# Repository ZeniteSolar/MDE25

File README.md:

<!-- PROJECT LOGO -->
<br />
<div align="center">

  <h3 align="center">Módulo de Direção Elétrica 2025 (MDE25)</h3>
</div>

# Visão Geral do Sistema

O sistema de direção elétrica do barco solar é composto por duas placas interligadas, uma de controle e outra de potência. O propósito do sistema é ser capaz de controlar o leme do barco conforme comandos recebidos pela rede CAN do barco enviados pelo Módulo Interface de Controle (MIC).

O barco contém atualmente a revisão [MDE22](https://github.com/ZeniteSolar/MDE22). Como pode ser visto, atualmente o barco contém uma bateria auxiliar de 12V dedicada para alimentar o sistema de direção elétrica, algo que não é tão proveitoso, sendo que o barco possui um banco de baterias principal que é mais que capacitado para alimentar o sistema de direção elétrica. Assim sendo, a bateria auxiliar implica em peso e eletrônica adicional, sendo que requer um Módulo de Carregamento de Bateria Auxiliar.

Tendo em vista a fundamentação acima, a revisão 2025 (MDE25) tem por objetivo:

* Remover a bateria auxiliar de 12V
* Utilizar o banco de baterias principal para alimentar o sistema de direção elétrica
* Melhorar aspectos gerais do sistema, velocidade de resposta, confiabilidade, etc.

Assim sendo, os requisitos abaixo foram definidos, vale notar que vários dos valores já são conhecidos de revisões anteriores, por isso não serão abordados aqui, mas podem ser encontrados no GitHub da [Zenite Solar](https://github.com/ZeniteSolar).

## Requisitos

* Tensão de entrada: 10-60V
* Tensão de saída: 10-60V
* Corrente média nominal: 20-30A
* Corrente média máxima: 42A
* Corrente de pico máxima: 80A
* Full Bridge (Reversão Completa)

## Estrutura do Projeto

Para o desenvolvimento do sistema, tendo em vista que a fabricação das placas foi realizada localmente, ou seja, não se atinge qualidade de empresas especializadas, foi decidido que o sistema seria desenvolvido em duas placas, uma de controle e outra de potência. Permitindo tolerância a erros de fabricação maiores e facilitando a fabricação e manutenção em geral.

---

### 1. Placa de Controle

A placa de controle é responsável por realizar a parte lógica do sistema, bem como gerar as tensões baixas, $V_{DDs}$ em geral e $V_{drive}$. Assim sendo, é constituída majoritariamente por um microcontrolador, um transceptor CAN, e um conjunto de conversores Step-Down / LDOs responsáveis por gerar as tensões necessárias para o sistema.

#### Componentes Principais

* **Microcontrolador:** STM32L431
* **Comunicação:** Rede CAN a 500 kbit/s baseado no transceptor MCP2561.
* **Interfaces:**
  * Conector CAN (também fornece 18 V para alimentação)
  * UART / ST-LINK para programação e depuração
  * Conector para sensor de posição do leme (potenciômetro)
  * Conectores para encoder e fim de curso (redundância)

---

### 2. Placa de Potência

A placa de potência é um sistema extremamente simples, sendo suas únicas funções controlar o motor utilizando uma Ponte H conforme sinais de PWM recebidos da placa de controle, prover sinais de medição, ou seja (Tensão de entrada, Tensão de saída e Corrente de entrada), sendo esses já tratados para serem convertidos pelo ADC do microcontrolador da placa de controle.

## Componentes Principais

* **Topologia:** Ponte H (full-bridge) com dois drivers UCC27211DDAR e quatro MOSFETs BSC093N15NS5.
* **Sensoriamento:**
  * Corrente: shunt de 1 mΩ + amplificador de instrumentação (INA283)
* Tensão: divisor resistivo com filtro passa-baixa de 40 Hz, objetivo de reduzir ruído de chaveamento/ringing.
* **Conectores:**
  * Alimentação principal via KRE (baterias chumbo-ácido 30-42 V ou lítio até 60 V)
  * Saída para motor modelo CIM (modelo FR801‑001)
* **Dissipação térmica:**
  * 5 vias de cobre (Ø 0,7 mm) por MOSFET
  * Thermal pad de 1 mm de espessura e 1 cm² por MOSFET
  * Dissipador montado entre as placas

---

# Fluxo de Sinal e Potência

1. **Entrada de Comando:**
   A placa MIC mede a posição do volante e transmite via CAN o setpoint da posição do leme através da mensagem `CAN_MSG_MIC19_MDE_ID`.

2. **Leitura e Controle:**
   O STM32L431 recebe o comando via CAN, valida o ID e seta o setpoint no controlador PID (utilizando apenas ganho proporcional devido a testes anteriores revelarem conflito entre piloto e ganho integral), que por consequência ajusta o PWM dos drivers conforme o erro entre o setpoint e a posição do leme.

3. **Ponte H:**
   Os drivers UCC27211 acionam os MOSFETs BSC093N15NS5 conforme o PWM gerado. Sendo que pode ser controlada tanto a direção quanto a velocidade do motor através da direção da corrente estabelecida pelo chaveamento e o duty cycle do PWM.

4. **Motor e Feedback:**
   O motor movimenta o leme, cuja posição é retroalimentada via um potenciômetro de 10 kΩ acoplado ao eixo e lido pelo ADC do STM32L431, que por sua vez atualiza a posição atual no controlador PID.

5. **Proteções e Limites:**
   * Monitoramento de corrente via shunt
   * Faixa de tensão de entrada: 10 V a 60 V
   * Faixa de tensão de saída: 0 V a 12 V (Motor projetado para 12 V)
   * Corrente média operacional: 20–30 A (No uso normal do barco)
   * Corrente contínua máxima: 42 A (com eixo travado até a queima) com picos de 80 A.
   * Potência média máxima: 425 W (Teste realizado até a queima da ponte H por incapacidade de dissipação e consequente dessolda dos MOSFETs)
   * Dissipador alcançou 60 C após 2 minutos de teste com reversão contínua, ou seja, ir de um extremo ao outro do leme (condição não usual)

---

# Etapas da Placa de Potência

## Entrada

Função de receber a tensão da bateria principal e alimentar a ponte H. Possui um fusível de 20 A para proteção e um banco de capacitores para estabilização da tensão que será utilizada pela ponte H.

* Conector KRE de alimentação (bateria principal)
* Fusível de 20 A
* Shunt de 1 mΩ para medição de corrente
* Filtros:
  * 2 × 470 µF eletrolíticos
  * 4 × 1 µF cerâmicos para redução de ripple e compensação de indutâncias parasitas

---

## Drivers

Os drivers são responsáveis por converter o sinal de PWM (Baixa tensão 3.3V e baixa capacidade de corrente) para um sinal de gate apropriado para os MOSFETs, além de que, por se tratar de uma ponte H completa, é necessário um driver com capacidade de chavear MOSFETs high-side e low-side. Assim sendo, foram utilizados dois drivers UCC27211DDAR, um para cada braço da ponte H. Mais especificações podem ser encontradas no datasheet do driver [UCC27211DDAR](https://www.ti.com/lit/ds/symlink/ucc27211.pdf) e no texto abaixo.

* 2 × UCC27211DDAR (meia ponte, tecnologia bootstrap)
* Acionamento complementar com limitação de corrente de gate por resistores de 62 Ω, ajustado em laboratório conforme notas de aplicação [External Gate Resistor Design Guide for Gate Drivers](https://www.ti.com/lit/ab/slla385a/slla385a.pdf)
* Resistores de 10 kΩ entre gate e source para evitar operação na região linear quando em alta impedância.
* Proteções adicionais conforme [Bootstrap Circuitry Selection for Half-Bridge
Configurations](https://www.ti.com/lit/an/slua887a/slua887a.pdf):
  * 2 diodos para proteção
  * Resistor de 2 Ω para limitar corrente de bootstrap

---

## Ponte H (MOSFETs + Snubber)

A ponte H é composta por quatro MOSFETs, dois para cada braço da ponte H, sendo que cada braço é composto por um MOSFET high-side e um MOSFET low-side, permitindo a reversão completa do motor e controle de velocidade através do duty cycle do PWM.

* 4 × BSC093N15NS5 (150 V, 87 A, R<sub>DS(on)</sub> = 9,3 mΩ)
* Proteção por snubber com TVS de 111 V (breakdown), 160 V (clamping)
* Estratégia de chaveamento:

  * Um braço da ponte permanece fixo (conduzindo), o outro chaveia.
  * O braço fixo alterna de acordo com o sentido do motor.
  * Para evitar sobrecarga no bootstrap, é garantido no controlador que o MOSFET acionado no braço fixo seja sempre o MOSFET low-side, assim sendo, o bootstrap não será completamente descarregado, pois o MOSFET high-side não conduzirá, evitando entrada na região linear dos MOSFETs.

---

## Sensor de Corrente (Entrada)

* Shunt de 1 mΩ + amplificador INA283 (ganho de 50 V/V)
* Saturação a 3,3 V → Corrente máxima medida ≈ 66 A

---

## Sensor de Tensão (Entrada e Saída)

* Divisor resistivo para adequar até 60 V para 2,6 V
* Filtro passa-baixa de 100 nF a 40 Hz
* Margem contra saturação do ADC e interferência do zener de proteção (3,3 V)
> Para medição da tensão de saída deve ser utilizado modo diferencial do ADC, assim sendo possível a medição da tensão tanto positiva quanto negativa. Isso ocorre pois, dependendo do sentido da corrente, a tensão de saída pode ser positiva ou negativa.

---

# Placa de Controle

A placa de controle, como já mencionado, é responsável por realizar as seguintes funções:

* Gerar níveis de tensão baixos (15V, 5V, 3.3V), note-se que o conector RJ45 da rede CAN já fornece 18V.
* Receber o setpoint desejado pelo piloto através da rede CAN.
* Monitorar a posição do leme através do potenciômetro.
* Gerar uma ação de controle para o motor através do PWM.

* Alimentação lógica e dos drivers por 18 V da rede CAN
* Comunicação CAN conforme padrão do barco solar
* MCU STM32L431:
  * Leitura de posição do leme (potenciômetro via ADC)
  * Implementação do controle proporcional
  * Geração do PWM de controle para os drivers

# Implementação do Projeto

Dado que praticamente todos os componentes já eram impostos (Já existiam no inventário da Zenite Solar e não podiam ser adquiridos novos atualmente), o projeto foi simplesmente a realização dos requisitos. Assim sendo, foi utilizado o software KiCad para a elaboração do projeto.

[Esquemático da Placa de Controle](./hardware/control/outputs/control.pdf)

[Esquemático da Placa de Potência](./hardware/power/outputs/power.pdf)

Com o projeto em mãos, foi realizada a fabricação das placas, ambas placas foram fabricadas localmente utilizando-se a técnica de fotolitografia com tinta UV e uma impressora de resina Elegoo Mars 2 PRO para a exposição UV. Os químicos utilizados foram os padrões para esse tipo de processo (Carbonato de Sódio 1%, Percloreto de Ferro e Acetona). Após a manufatura, ambas placas foram estanhadas, tendo em vista que o ambiente de trabalho é propenso à corrosão e o estanhamento melhora a vida útil das placas.

## Placa de Controle

## Placa de Potência

## Placa de controle montada

## Placa de potência montada

## Sistema de dissipação térmica

## MDE25 - Montagem Final

---

# Testes

Para monitoramento/ajustes, um pequeno aplicativo Python foi desenvolvido, pode-se encontrar [Aqui](./firmware/Extra/TelemetryPanel/panel.py). Esse aplicativo foi utilizado para verificar comportamento do sistema e ajustar o controlador PID.

## Simples exemplo de um teste em hardware real (Direção + Leme) aproximando uma resposta ao degrau

## Simples exemplo de um teste em hardware real (Direção + Leme) aproximando um setpoint seguindo uma onda triangular

Como pode ser visto, o sistema operou corretamente conforme o esperado, abaixo mais detalhes sobre os testes são apresentados.

## Limite a limite velocidade constante

Foi realizado um teste com o volante indo de limite a limite a velocidade constante:

* O motor leva cerca de 1s para atingir o extremo oposto (Ótimo tempo de resposta)
* Na reversão, consome cerca de 40 A por 500 ms
* Corrente estabiliza em torno de 11 A após aceleração
* Temperatura do dissipador atingiu 60 C após 2 min de teste contínuo (Esse comportamento de teste contínuo não é um caso esperado que o piloto realize em operação normal)

## Teste de queima

Após a validação do sistema, desejou-se testar a capacidade de sobrecarga do MDE25, para assim entender os limites e como o sistema vem a falhar. Para isso, o eixo do leme foi travado e o piloto comandou a direção de um extremo ao outro do leme.

As métricas do painel de monitoramento foram as seguintes:

Foi necessário cerca de 30 segundos para que o sistema entrasse em sobrecarga e viesse a queima. Como pode ser visto pelo painel, no momento em que entra em sobrecarga, a tensão na bateria principal caiu cerca de 4V. Indo de aproximadamente 38V para 34V, isso demonstra que um estresse muito grande foi aplicado ao sistema, tendo em vista que se trata de um banco de baterias de chumbo com alta capacidade de corrente. Após a queima, o sistema foi desmontado e averigou-se a causa da queima.

## Detalhes da queima e notas sobre o sistema

Dado que os MOSFETs utilizados realizam a sua troca de calor com o dissipador por um pad térmico, ou seja, a transferência não é realizada pelo case do componente, mas sim pelo seu pad de dreno, é necessário que a placa seja capaz de conduzir esse calor de forma efetiva para o dissipador, assim foram feitas vias de cobre (5 vias de 0.7mm para cada MOSFET). Segue abaixo a foto das vias térmicas.

Como pode ser observado, um dos conjuntos de vias ficou apenas com 3 vias efetivamente transferindo calor, pois 2 acabaram sendo lixadas pelo processo de fabricação, isso resultou com que o MOSFET associado com essas vias viesse a sobreaquecer e dessoldar, não sendo o calor diretamente a causa da queima, mas sim a dessolda do MOSFET que resultou em uma gota de solda dando curto no braço da ponte H e após isso gerando a queima. Segue foto do MOSFET queimado.

<div style="text-align: center; max-width: 20%; margin: 0 auto;">
  
</div>

# Notas extras sobre estimativa da Indutância do Motor

Para estimar a indutância do motor, utilizamos o ripple de corrente observado em regime permanente com o motor em velocidade constante.

## Parâmetros do teste:

* Corrente média: **11 A**
* Ripple de corrente: **10%** → $\Delta I = 1{,}1\,\text{A}_{pp}$
* Tensão de alimentação: **36 V**
* Duty cycle: **40%**
* Frequência de PWM: **20 kHz** (→ período $T_s = 50\,\mu\text{s}$)
* Topologia: **Ponte H full-bridge com modulação bipolar**

## Modelo de cálculo:

Assumindo modulação bipolar, a variação de corrente durante o ciclo de comutação é dada por:

$$
\Delta I = \frac{2 \cdot V \cdot D \cdot T_s}{L}
\Rightarrow
L = \frac{2 \cdot V \cdot D \cdot T_s}{\Delta I}
$$

Substituindo os valores:

$$
L = \frac{2 \cdot 36\,\text{V} \cdot 0{,}4 \cdot 50 \times 10^{-6}\,\text{s}}{1{,}1\,\text{A}}
= \frac{1{,}44 \cdot 10^{-3}}{1{,}1}
\approx 1{,}31\,\text{mH}
$$

## Resultado:

A indutância estimada do motor é:

$$
\boxed{L \approx 1{,}31\;\text{mH}}
$$

# Sobre o Firmware

## Arquitetura de Software

O firmware está organizado em módulos funcionais especializados:
- **Core/control**: Implementação do controlador PID
- **Core/pwm**: Geração de sinais PWM para ponte H
- **Core/sense**: Aquisição de dados via ADC
- **Core/CAN**: Servidor de comunicação CAN
- **Core/uart_server**: Interface de debug e configuração
- **Core/telemetry**: Sistema de monitoramento
- **Core/status**: Gerenciamento de estado e feedback sonoro

## Configuração do Sistema

O firmware possui diversos parâmetros que podem ser ajustados para otimizar o sistema para as necessidades do usuário, esses podem ser ajustados no arquivo de configuração [config.h](./firmware/Core/Inc/config.h).

## Módulos de Firmware

### 1. Módulo de Controle (Core/control)

#### Funcionalidades Principais
O módulo implementa um controlador PID digital completo (control.c) com as seguintes características técnicas:

**Parâmetros de Controle:**
- Ganho Proporcional (Kp): 2.8 (inicial, configurável)
- Ganho Integral (Ki): 0.0 (inicial, configurável)
- Ganho Derivativo (Kd): 0.0 (inicial, configurável)
- Janela de média móvel: 15 amostras para filtragem de setpoint para evitar mudança abrupta de setpoint.

**Algoritmo PID:**
```
error = setpoint - feedback
integral += error * dt
integral = clamp(integral, -0.1, 0.1)  // Anti-windup
derivative = (error - error_previous) / dt
output = Kp * error + Ki * integral + Kd * derivative
```

**Características de Implementação:**
- **Filtragem de Setpoint** (control.c): Média móvel de 15 amostras para suavizar comandos de entrada e reduzir oscilações
- **Saturação de Saída**: Limitação entre -1.0 e +1.0 com zona morta configurável
- **Anti-windup**: Limitação da integral entre -0.1 e 0.1 para evitar saturação
- **Período Dinâmico**: Baseado na frequência real de amostragem do ADC
- **Lock de Setpoint**: Capacidade de travamento para operação manual

### 2. Módulo PWM (Core/pwm)

#### Geração de Sinais PWM
O módulo controla a ponte H através de dois canais PWM complementares (pwm.c):

**Especificações Técnicas:**
- **Timer**: TIM1 (Advanced Timer) utilizado para gerar os sinais PWM.
- **Frequência Base**: 24 kHz (configurável acima de 1.3 kHz)
- **Resolução**: 16 bits
- **Canais**: CH1 e CH2 com saídas complementares (CHxN)

**Compensação de Tensão** (pwm.c):
O sistema implementa compensação automática baseada na tensão de entrada:
```
max_duty = PWM_MAX_OUT_VOLTAGE / clamped_input_voltage;
effective_duty = map(input_duty, -1.0, 1.0, -max_duty, max_duty);
```

**Características de Segurança:**
- **Zona Morta**: Configurável (-0.06 a +0.06) para evitar vibrações e perda de energia sem realização de movimento útil.

#### Configurações
- **Tensão Máxima de Saída (Ajustável)**: 12V
- **Faixa de Tensão de Entrada**: 24V a 60V
- **Dead Time**: Configurado para proteção da ponte H, otimizado em laboratório para melhor tempo sem gerar curto no braço.

### 3. Módulo de Sensoriamento (Core/sense)

#### Aquisição de Dados ADC
Sistema de conversão analógico-digital de 4 canais simultâneos (sense.c:10-16):

**Canais de Conversão:**
```
typedef enum {
  ADC_RANK_CURRENT_CONTROL_POINT = 0U,  // Posição do leme
  ADC_RANK_INPUT_VOLTAGE = 1U,           // Tensão de entrada
  ADC_RANK_OUTPUT_VOLTAGE = 2U,          // Tensão de saída
  ADC_RANK_INPUT_CURRENT = 3U,           // Corrente de entrada
} adc_ranks_t;
```

**Características Técnicas:**
- **Resolução**: 16 bits (65535 níveis) (Com Oversample, dado cru 12 bits)
- **Modo**: Conversão contínua via DMA
- **Trigger**: Timer 2 (frequência configurável) atrelado também a atualização da malha de controle.
- **Buffer**: Circular DMA para aquisição contínua

**Calibração e Linearização:**
Cada canal possui calibração específica (sense.c), calibrações do ADC podem ser feitas utilizando o seguinte [script](./firmware/Extra/ADC_Linearization/linearization.py):
- **Tensão de Entrada**: `V = 0.001150 * ADC - 0.088064`
- **Tensão de Saída**: `V = 0.002327 * ADC - 73.731254`
- **Posição**: `P = (ADC * 2.0 / 65535.0) - 1.0` (normalizada ±1.0)
- **Corrente**: `I = ADC * 3.3 / 65535.0` (referência 3.3V)

### 4. Servidor CAN (Core/CAN)

#### Protocolo de Comunicação
Implementa cliente CAN para recepção de comandos do MIC19 (can_server.c):

**Filtro CAN** (can_server.c):
- **Modo**: ID Mask para filtragem seletiva
- **Banco**: 0 (FIFO0)
- **Máscara**: 0x7FF (11 bits de ID padrão)

**Especificações do Protocolo:**
- **ID da Mensagem**: 31 (CAN_MSG_MIC19_MDE_ID)
- **Comprimento**: 4 bytes
- **Frequência**: 50 Hz
- **Assinatura**: 240 (CAN_SIGNATURE_MIC19)

**Estrutura da Mensagem:**
```
Byte 0: Assinatura (240)
Byte 1: Position_L (8 bits baixos)
Byte 2: Position_H (8 bits altos)
Byte 3: Reservado
```

**Processamento de Dados** (can_server.c):

Normalização do setpoint -1.0 a 1.0:

```
uint16_t position = rxData[1] | (rxData[2] << 8);
float steering_angle = (position / 1024.0f) * 2.0f - 1.0f;
```

#### Sistema de Watchdog
**Timeout de Comunicação** (can_server.c):
- **Timer**: TIM7 para detecção de perda de comunicação
- **Reset Automático**: Contador zerado a cada mensagem válida
- **Ação de Timeout**: Setpoint zerado e status de desconexão. Gera sinal sonoro de sequência específica de BEEP no motor. Reconexão também irá resultar em sinal sonoro de sequência específica de BEEP no motor.

### 5. Servidor UART (Core/uart_server)

#### Interface de Debug e Configuração
Sistema de comunicação serial para debug e ajuste de parâmetros (uart_server.c):

**Protocolo de Comando:**
- **Formato**: `<comando:valor>`
- **Delimitadores**: `<` (início) e `>` (fim)
- **Parser**: Máquina de estados para robustez
- **Buffer**: 128 bytes com buffer circular

**Comandos Disponíveis:**
```
'D': Set PWM duty cycle (-1.0 a 1.0)
'F': Set PWM frequency (Hz)
'p': Set PID proportional gain
'i': Set PID integral gain
'd': Set PID derivative gain
's': Set ADC sampling frequency
'L': Lock/unlock PWM (1/0)
'R': System reset
```

#### Implementação do Parser
**Máquina de Estados** (uart_server.c):
```
UART_SERVER_STATE_WAIT_START      -> Aguarda '<'
UART_SERVER_STATE_WAIT_TERMINATOR -> Coleta dados até '>'
UART_SERVER_STATE_NEW_MESSAGE     -> Mensagem completa
UART_SERVER_STATE_ERROR           -> Overflow ou erro
```
### 6. Sistema de Telemetria (Core/telemetry)

#### Estrutura de Dados
Coleta e transmite métricas do sistema (telemetry.h):

```
typedef struct {
  uint16_t preamble;           // 0x5A54
  float sense_input_voltage;   // Tensão de entrada
  float sense_input_current;   // Corrente de entrada
  float sense_output_voltage;  // Tensão de saída
  float sense_control_point;   // Posição atual
  float control_setpoint;      // Setpoint desejado
  float control_error;         // Erro de controle
  float pwm_duty;             // Duty cycle nominal
  float pwm_effective_duty;   // Duty cycle efetivo
  uint8_t status_connected;   // Status de conexão
} telemetry_t;
```

**Características de Transmissão:**
- **Frequência**: 40 Hz (intervalo de 25ms)
- **Interface**: UART a 115200 bps
- **Formato**: Printf formatado para debug
- **Habilitação**: Condicional via DEBUG_TELEMETRY_ENABLE

#### Saída de Debug
Formato de telemetria (telemetry.c):
```
"VI:%f, II:%f, VO:%f, CP:%f, SP:%f, ER:%f, D:%f, ED:%f, ST:%hu\n"
```

### 7. Módulo de Status (Core/status)

#### Sistema de Feedback Sonoro
Gerencia indicação sonora de estado do sistema (status.c):

**Sequências de Status:**
- **Conexão**: 3 tons crescentes (Baixo → Médio → Alto)
- **Desconexão**: 3 tons decrescentes (Alto → Médio → Baixo)
- **Desconectado**: Tom único alto

**Parâmetros Sonoros:**
```
#define STATUS_TONE_FREQUENCY_LOW_HZ    2093.0f  // C7
#define STATUS_TONE_FREQUENCY_MEDIUM_HZ 2794.0f  // F7
#define STATUS_TONE_FREQUENCY_HIGH_HZ   4186.0f  // C8
#define STATUS_TONE_DURATION_S          0.16f
#define STATUS_TONE_PWM_VOLUME          0.70f
```

#### Implementação Técnica
**Geração de Tom** (status.c):
- **Timer**: TIM6 para base de tempo
- **Modulação**: PWM alternado entre +70% e -70%
- **Cálculo de Frequência**: `repetitions = duration / (1/frequency)`
- **Callback**: Sistema de callbacks encadeados para sequências

**Controle de Estado:**
- **Variável Global**: `device_connected` para rastreamento
- **Transições**: Apenas em mudanças de estado
- **Proteção**: Evita múltiplas execuções da mesma sequência

### 8. Utilitários Matemáticos (utils.h)

```
float clampf(float value, float min, float max);
// Limita valor entre mínimo e máximo

float passf(float value, float replace, float cut_min, float cut_max);
// Zona morta - substitui valores dentro de faixa

float mapf(float value, float min_in, float max_in, float min_out, float max_out);
// Mapeia valor de uma faixa para outra
```

### Configuração de Periféricos
**Timers Utilizados:**
- **TIM1**: PWM principal (24 kHz, centro-alinhado)
- **TIM2**: Trigger para ADC (frequência configurável)
- **TIM6**: Base de tempo para status sonoro
- **TIM7**: Watchdog de comunicação CAN

**DMA Channels:**
- **ADC1**: Conversão contínua 4 canais
- **UART1**: Recepção com idle detection

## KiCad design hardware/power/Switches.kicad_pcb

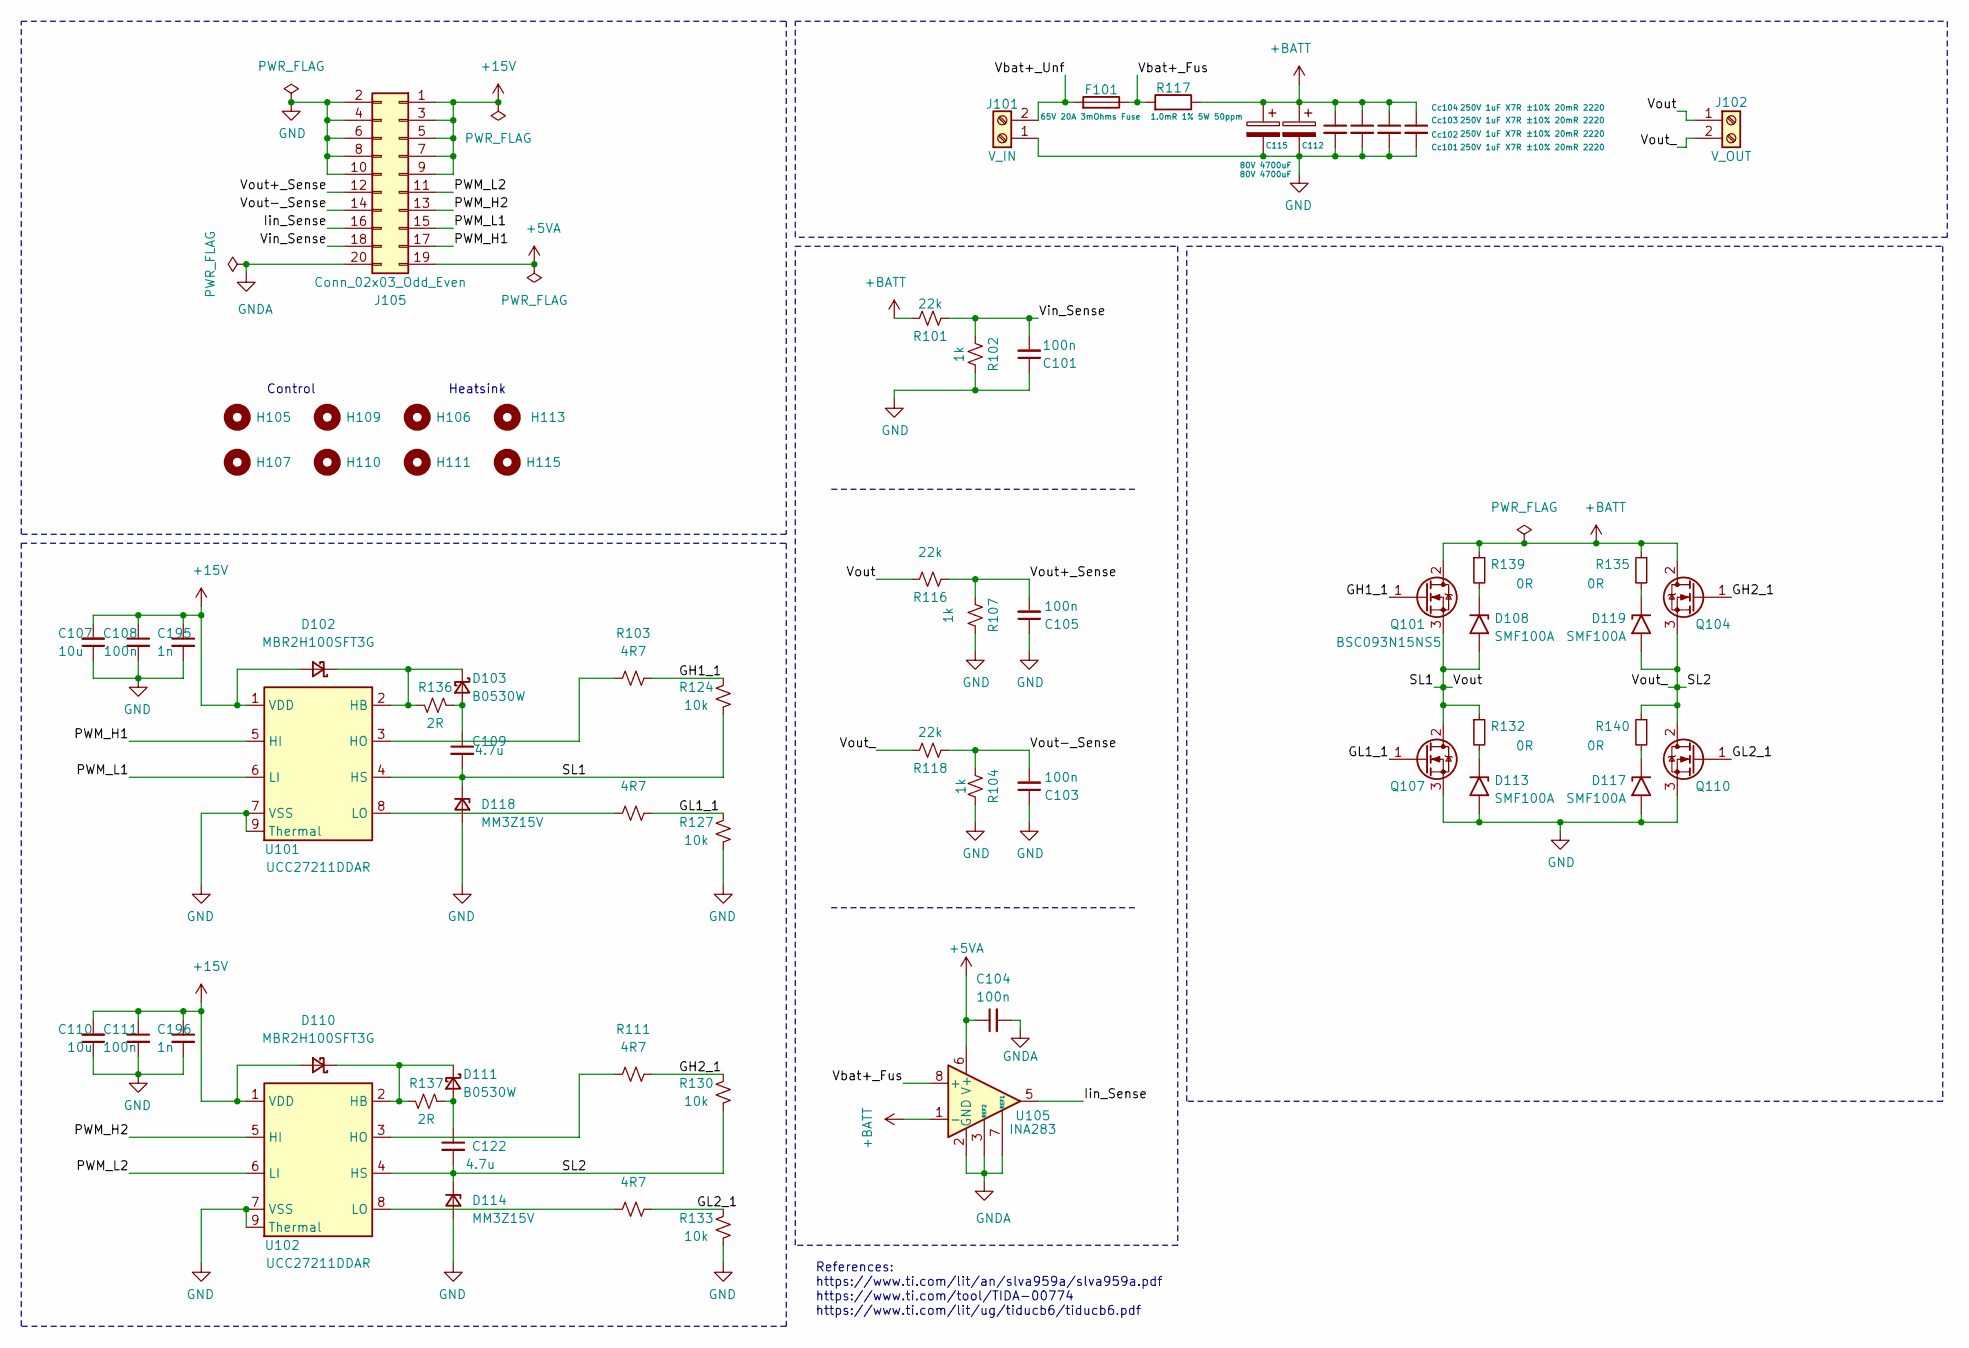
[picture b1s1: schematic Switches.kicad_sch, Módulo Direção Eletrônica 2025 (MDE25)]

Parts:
C101, C103, C104, C105, C108, C111: 100n; C_0805_2012Metric_Pad1.18x1.45mm_HandSolder
C107, C110: 10u; C_1210_3225Metric_Pad1.33x2.70mm_HandSolder
C109, C122: 4.7u; C_1210_3225Metric_Pad1.33x2.70mm_HandSolder
C112, C115: 80V 4700uF; CP_Radial_D12.5mm_P5.00mm
C195, C196: 1n; C_0805_2012Metric_Pad1.18x1.45mm_HandSolder
Cc101, Cc102, Cc103, Cc104: 250V 1uF X7R ±10% 20mR 2220; C_2220_5650Metric
D102, D110: MBR2H100SFT3G; D_SOD-123F
D103, D111: B0530W; D_SOD-123F
D108, D113, D117, D119: SMF100A; D_SOD-123F
D114, D118: MM3Z15V; D_SOD-123F
F101: 65V 20A 3mOhms Fuse; S6125-F
H105, H106, H107, H109, H110, H111, H113, H115: MountingHole; MountingHole_3.5mm_Pad
J101: V_IN; TerminalBlock_MaiXu_MX126-5.0-02P_1x02_P5.00mm
J102: V_OUT; TerminalBlock_MaiXu_MX126-5.0-02P_1x02_P5.00mm
J105: Conn_02x03_Odd_Even; PinHeader_2x10_P2.54mm_Vertical
Q101, Q104, Q107, Q110: BSC093N15NS5; TDSON-8-3
R101, R116, R118: 22k; R_0805_2012Metric_Pad1.20x1.40mm_HandSolder
R102, R104, R107: 1k; R_0805_2012Metric_Pad1.20x1.40mm_HandSolder
R103, R106, R111, R114: 4R7; R_0805_2012Metric_Pad1.20x1.40mm_HandSolder
R117: 1.0mR 1% 5W 50ppm; R_2512_6332Metric_Pad1.40x3.35mm_HandSolder
R124, R127, R130, R133: 10k; R_0805_2012Metric_Pad1.20x1.40mm_HandSolder
R132, R135, R139, R140: 0R; R_0805_2012Metric_Pad1.20x1.40mm_HandSolder
R136, R137: 2R; R_0805_2012Metric_Pad1.20x1.40mm_HandSolder
U101, U102: UCC27211DDAR; SOIC-8-1EP_3.9x4.9mm_P1.27mm_EP2.514x3.2mm
U105: INA283; SOIC-8_3.9x4.9mm_P1.27mm

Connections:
+5VA: C104.1, J105.19, U105.6 (V+)
+15V: C107.2, C108.1, C110.2, C111.1, C195.1, C196.1, D102.2 (A), D110.2 (A), J105.1, J105.3, J105.5, J105.7, J105.9, U101.1 (VDD), U102.1 (VDD)
+BATT: C112.1, C115.1, Cc101.1, Cc102.1, Cc103.1, Cc104.1, Q101.2 (D), Q104.2 (D), R101.2, R117.1, R135.1, R139.1, U105.1 (-)
/GH1_1: Q101.1 (G), R103.1, R124.2
/GH2_1: Q104.1 (G), R111.1, R130.2
/GL1_1: Q107.1 (G), R106.1, R127.2
/GL2_1: Q110.1 (G), R114.1, R133.2
/Iin_Sense: J105.16, U105.5
/PWM_H1: J105.17, U101.5 (HI)
/PWM_H2: J105.13, U102.5 (HI)
/PWM_L1: J105.15, U101.6 (LI)
/PWM_L2: J105.11, U102.6 (LI)
/SL1: C109.2, D108.2 (A2), D118.1 (K), J102.1, Q101.3 (S), Q107.2 (D), R116.2, R124.1, R132.1, U101.4 (HS)
/SL2: C122.2, D114.1 (K), D119.2 (A2), J102.2, Q104.3 (S), Q110.2 (D), R118.2, R130.1, R140.1, U102.4 (HS)
/Vbat+_Fus: F101.1, R117.2, U105.8 (+)
/Vbat+_Unf: F101.2, J101.2
/Vin_Sense: C101.2, J105.18, R101.1, R102.1
/Vout+_Sense: C105.2, J105.12, R107.1, R116.1
/Vout-_Sense: C103.2, J105.14, R104.1, R118.1
GND: C101.1, C103.1, C105.1, C107.1, C108.2, C110.1, C111.2, C112.2, C115.2, C195.2, C196.2, Cc101.2, Cc102.2, Cc103.2, Cc104.2, D113.2 (A2), D114.2 (A), D117.2 (A2), D118.2 (A), J101.1, J105.2, J105.4, J105.6, J105.8, J105.10, Q107.3 (S), Q110.3 (S), R102.2, R104.2, R107.2, R127.1, R133.1, U101.7 (VSS), U101.9 (Thermal), U102.7 (VSS), U102.9 (Thermal)
GNDA: C104.2, J105.20, U105.2 (GND), U105.3 (REF2), U105.7 (REF1)
unnamed: D102.1 (K), D103.1 (K), R136.1, U101.2 (HB)
unnamed: C109.1, D103.2 (A), R136.2
unnamed: D108.1 (A1), R139.2
unnamed: D110.1 (K), D111.1 (K), R137.1, U102.2 (HB)
unnamed: C122.1, D111.2 (A), R137.2
unnamed: D113.1 (A1), R132.2
unnamed: D117.1 (A1), R140.2
unnamed: D119.1 (A1), R135.2
unnamed: R103.2, U101.3 (HO)
unnamed: R106.2, U101.8 (LO)
unnamed: R111.2, U102.3 (HO)
unnamed: R114.2, U102.8 (LO)

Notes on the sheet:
Control
References: https://www.ti.com/lit/an/slva959a/slva959a.pdf https://www.ti.com/tool/TIDA-00774 https://www.ti.com/lit/ug/tiducb6/tiducb6.pdf
Heatsink

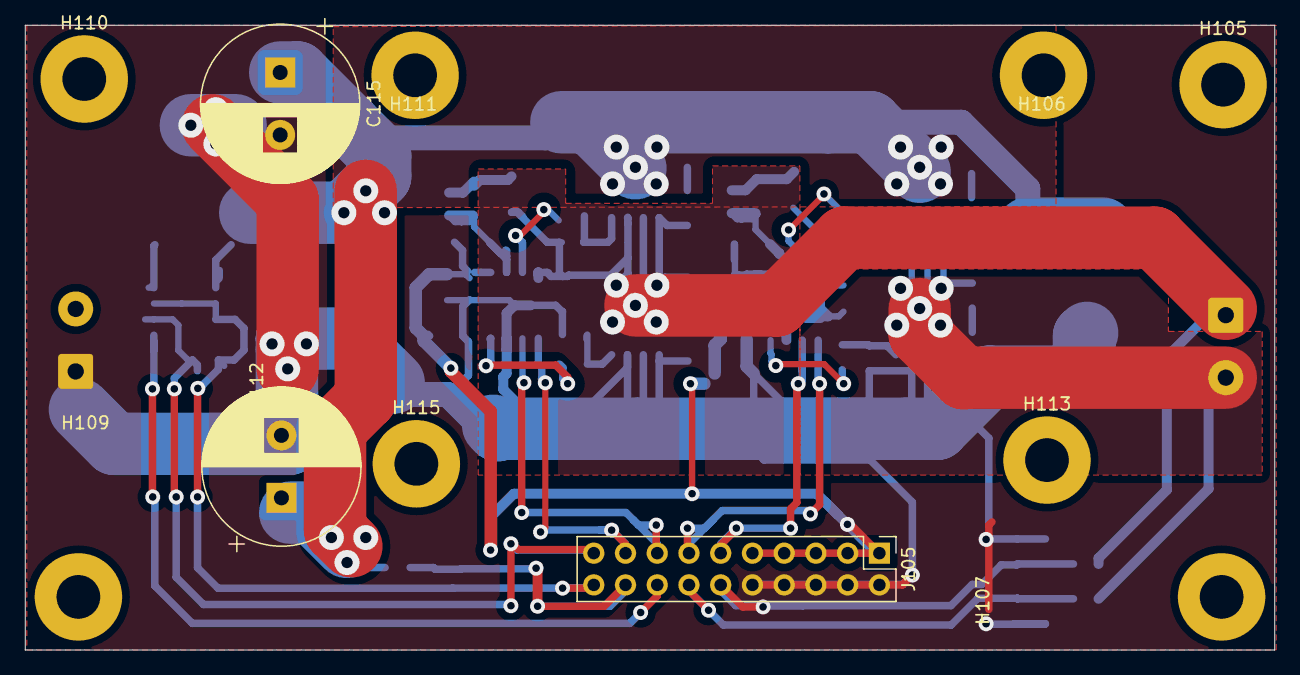
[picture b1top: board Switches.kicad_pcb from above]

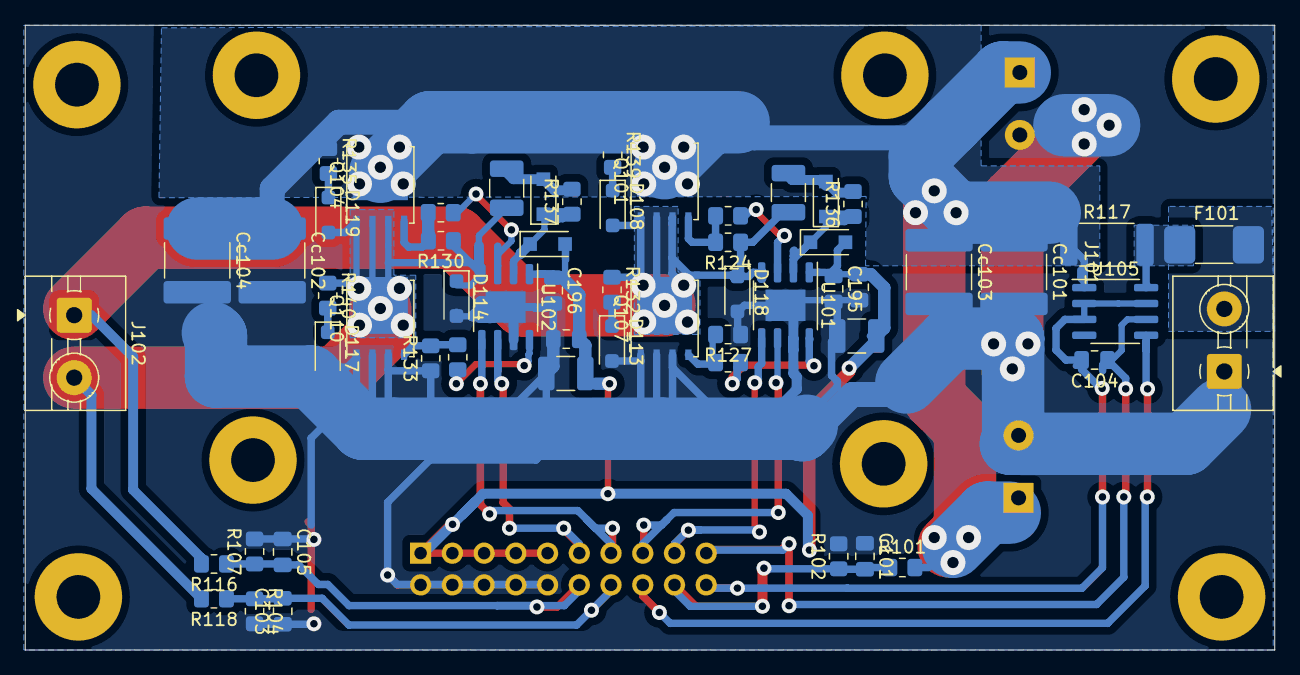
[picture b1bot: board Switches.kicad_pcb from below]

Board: 2 copper layers, 100.0 x 50.0 mm, 68 parts (57 on the bottom side), 33 nets.

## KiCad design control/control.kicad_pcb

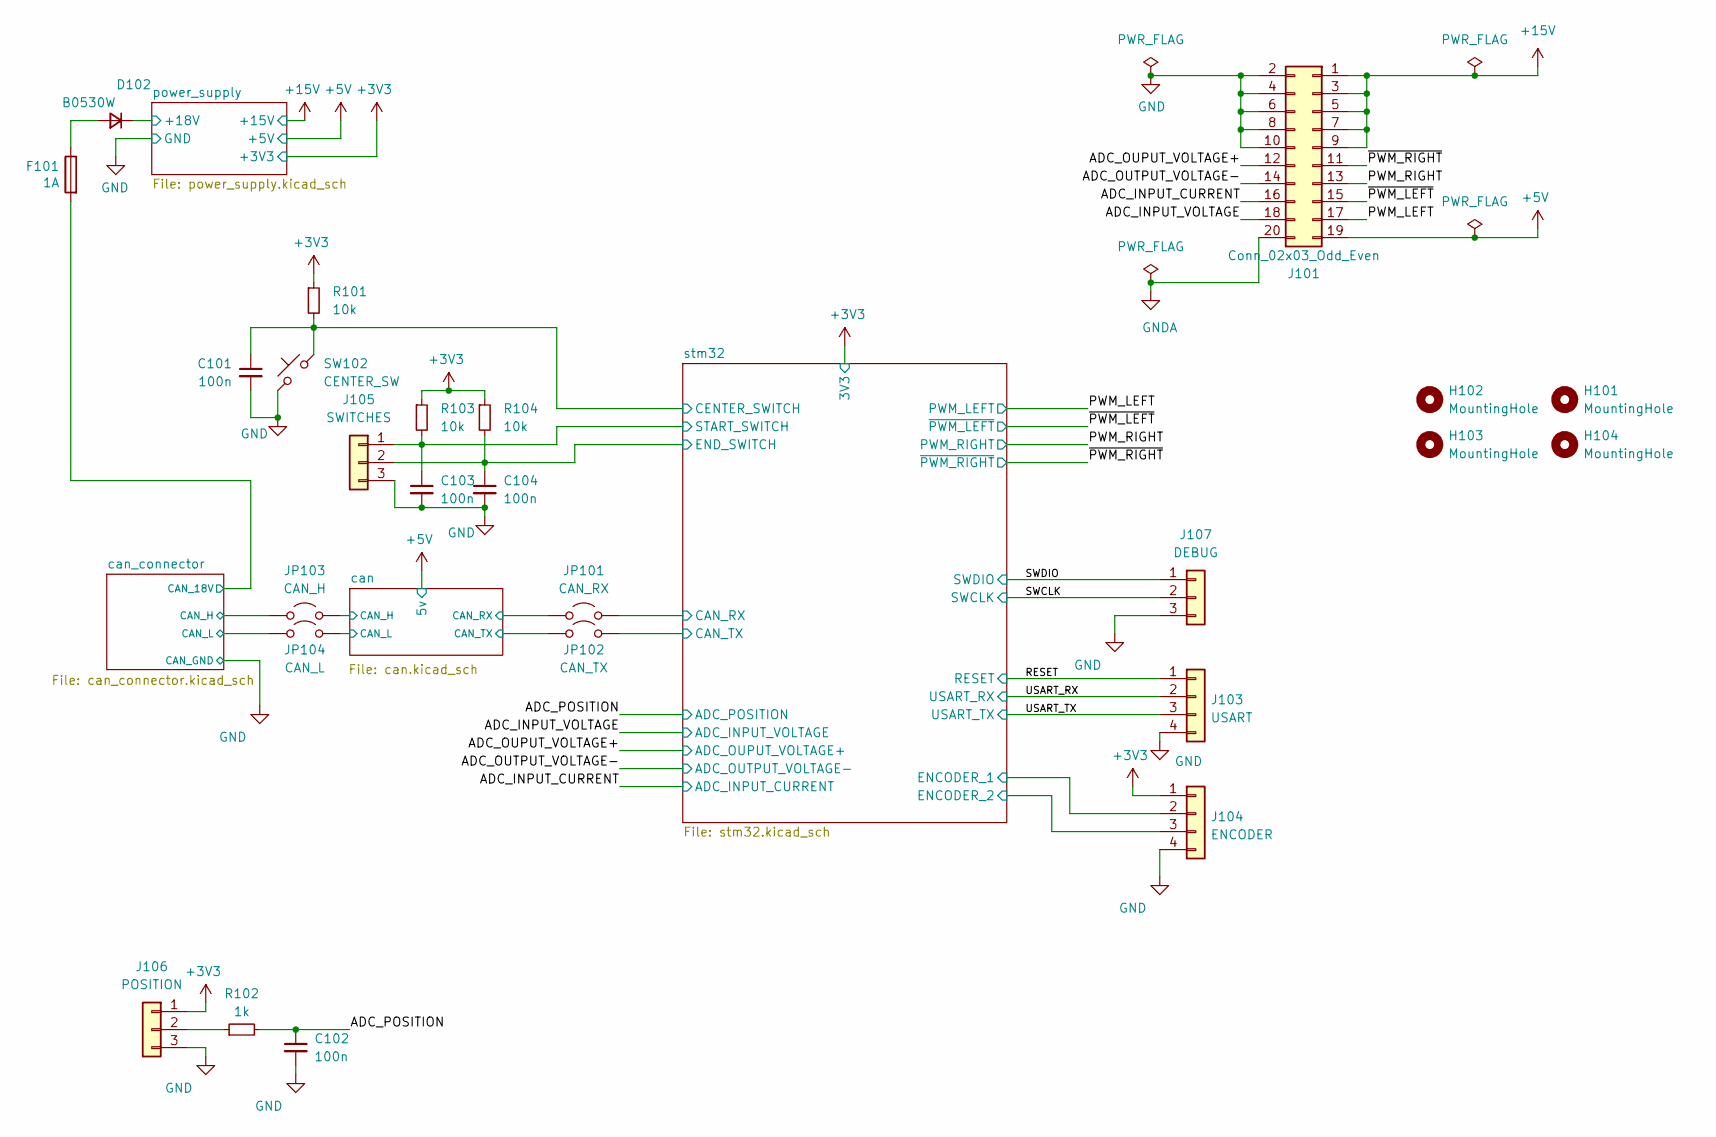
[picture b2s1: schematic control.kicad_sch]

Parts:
C101, C102, C103, C104: 100n; C_0805_2012Metric_Pad1.18x1.45mm_HandSolder
D102: B0530W; D_SOD-123F
F101: 1A; Fuse_1812_4532Metric_Pad1.30x3.40mm_HandSolder
H101, H102, H103, H104: MountingHole; MountingHole_3.2mm_M3
J101: Conn_02x03_Odd_Even; PinHeader_2x10_P2.54mm_Vertical
J103: USART; PinHeader_1x04_P2.54mm_Vertical
J104: ENCODER; TerminalBlock_bornier-4_P5.08mm
J105: SWITCHES; TerminalBlock_bornier-3_P5.08mm
J106: POSITION; TerminalBlock_bornier-3_P5.08mm
J107: DEBUG; PinHeader_1x03_P2.54mm_Vertical
JP101: CAN_RX; SolderJumper-2_P1.3mm_Open_TrianglePad1.0x1.5mm
JP102: CAN_TX; SolderJumper-2_P1.3mm_Open_TrianglePad1.0x1.5mm
JP103: CAN_H; SolderJumper-2_P1.3mm_Open_TrianglePad1.0x1.5mm
JP104: CAN_L; SolderJumper-2_P1.3mm_Open_TrianglePad1.0x1.5mm
R101, R103, R104: 10k; R_0805_2012Metric_Pad1.20x1.40mm_HandSolder
R102: 1k; R_0805_2012Metric_Pad1.20x1.40mm_HandSolder
SW102: CENTER_SW; SW_PUSH_6mm

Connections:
+3V3: J104.1, J106.1, R101.1, R103.1, R104.1; also elsewhere on the board
+5V: J101.19; also elsewhere on the board
+15V: J101.1, J101.3, J101.5, J101.7, J101.9; also elsewhere on the board
/ADC_INPUT_CURRENT: J101.16; also elsewhere on the board
/ADC_INPUT_VOLTAGE: J101.18; also elsewhere on the board
/ADC_OUPUT_VOLTAGE+: J101.12; also elsewhere on the board
/ADC_OUTPUT_VOLTAGE-: J101.14; also elsewhere on the board
/ADC_POSITION: C102.1, R102.2; also elsewhere on the board
/PWM_LEFT: J101.17; also elsewhere on the board
/PWM_RIGHT: J101.13; also elsewhere on the board
/RESET: J103.1; also elsewhere on the board
/SWCLK: J107.2; also elsewhere on the board
/SWDIO: J107.1; also elsewhere on the board
/USART_RX: J103.2; also elsewhere on the board
/USART_TX: J103.3; also elsewhere on the board
/can/CAN_H: JP103.1 (A); also elsewhere on the board
/can/CAN_L: JP104.1 (A); also elsewhere on the board
/can/CAN_RX: JP101.2 (B); also elsewhere on the board
/can/CAN_TX: JP102.2 (B); also elsewhere on the board
/can_connector/CAN_18V: F101.2; also elsewhere on the board
/can_connector/CAN_H: JP103.2 (B); also elsewhere on the board
/can_connector/CAN_L: JP104.2 (B); also elsewhere on the board
/power_supply/+18V: D102.1 (K); also elsewhere on the board
/stm32/CAN_RX: JP101.1 (A); also elsewhere on the board
/stm32/CAN_TX: JP102.1 (A); also elsewhere on the board
/stm32/CENTER_SWITCH: C101.1, R101.2, SW102.2; also elsewhere on the board
/stm32/ENCODER_1: J104.2; also elsewhere on the board
/stm32/ENCODER_2: J104.3; also elsewhere on the board
/stm32/END_SWITCH: C104.1, J105.2, R104.2; also elsewhere on the board
/stm32/START_SWITCH: C103.1, J105.1, R103.2; also elsewhere on the board
/~PWM_LEFT: J101.15; also elsewhere on the board
/~PWM_RIGHT: J101.11; also elsewhere on the board
GND: C101.2, C102.2, C103.2, C104.2, J101.2, J101.4, J101.6, J101.8, J101.10, J101.20, J103.4, J104.4, J105.3, J106.3, J107.3, SW102.1; also elsewhere on the board
unnamed: D102.2 (A), F101.1
unnamed: J106.2, R102.1

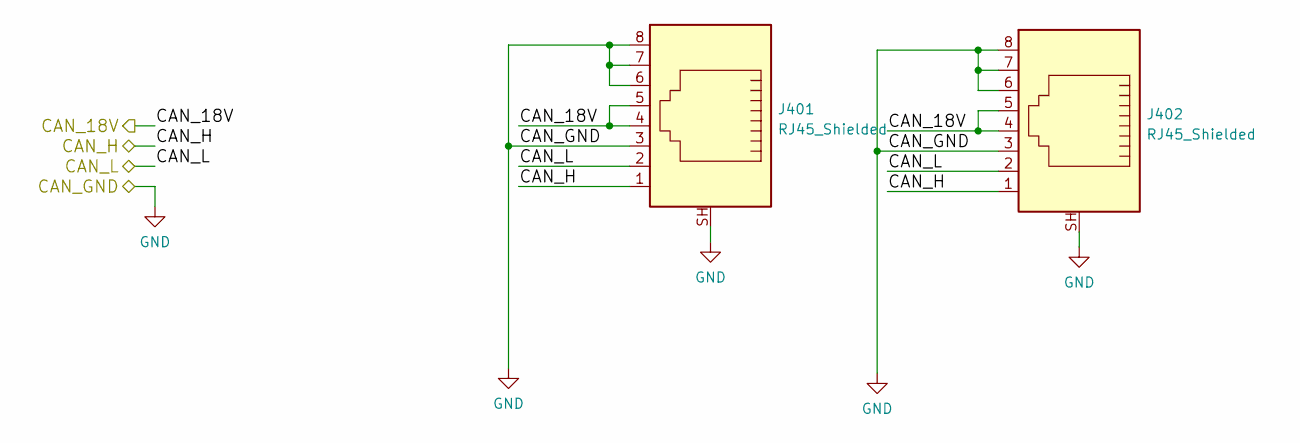
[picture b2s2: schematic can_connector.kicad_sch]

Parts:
J401, J402: RJ45_Shielded; RJ45_YH59_01

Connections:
/can_connector/CAN_18V: J401.4, J401.5, J402.4, J402.5; also elsewhere on the board
/can_connector/CAN_H: J401.1, J402.1; also elsewhere on the board
/can_connector/CAN_L: J401.2, J402.2; also elsewhere on the board
GND: J401.3, J401.6, J401.7, J401.8, J401.SH, J402.3, J402.6, J402.7, J402.8, J402.SH; also elsewhere on the board

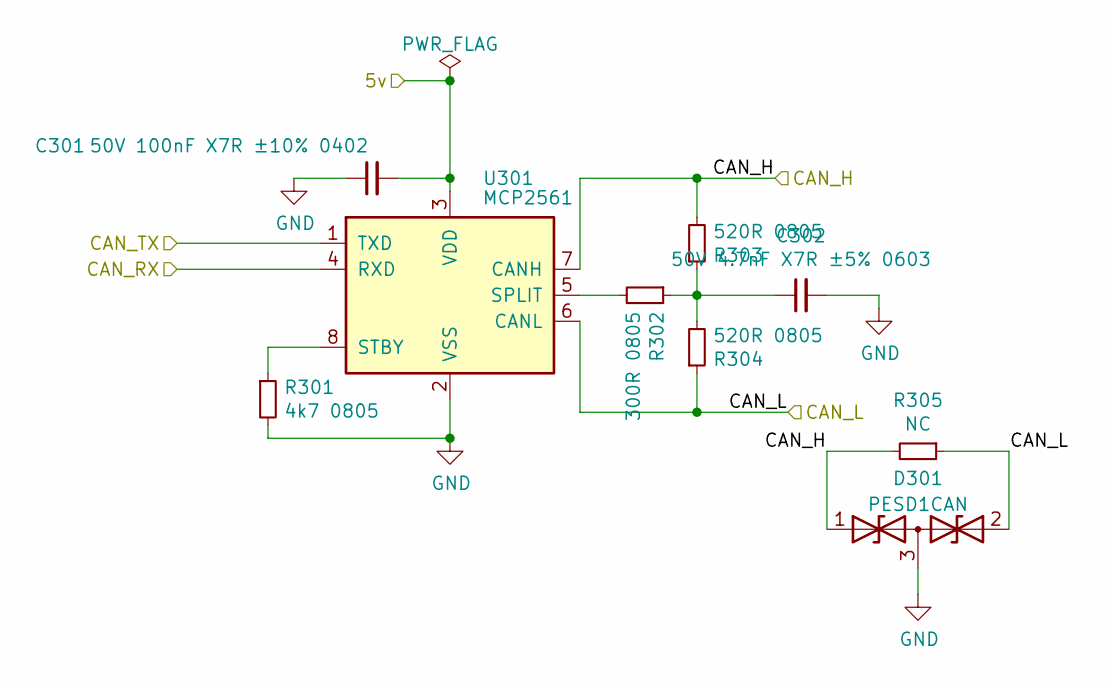
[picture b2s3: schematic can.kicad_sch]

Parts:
C301: 50V 100nF X7R ±10% 0402; C_0805_2012Metric_Pad1.18x1.45mm_HandSolder
C302: 50V 4.7nF X7R ±5% 0603; C_0805_2012Metric_Pad1.18x1.45mm_HandSolder
D301: PESD1CAN; SOT-23_Handsoldering
R301: 4k7 0805; R_0805_2012Metric_Pad1.20x1.40mm_HandSolder
R302: 300R 0805; R_0805_2012Metric_Pad1.20x1.40mm_HandSolder
R303, R304: 520R 0805; R_0805_2012Metric_Pad1.20x1.40mm_HandSolder
R305: NC; R_0805_2012Metric_Pad1.20x1.40mm_HandSolder
U301: MCP2561; SOIC-8_3.9x4.9mm_P1.27mm

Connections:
+5V: C301.2, U301.3 (VDD); also elsewhere on the board
/can/CAN_H: D301.1 (A1), R303.2, R305.2, U301.7 (CANH); also elsewhere on the board
/can/CAN_L: D301.2 (A2), R304.1, R305.1, U301.6 (CANL); also elsewhere on the board
/can/CAN_RX: U301.4 (RXD); also elsewhere on the board
/can/CAN_TX: U301.1 (TXD); also elsewhere on the board
GND: C301.1, C302.2, D301.3 (common), R301.2, U301.2 (VSS); also elsewhere on the board
unnamed: C302.1, R302.1, R303.1, R304.2
unnamed: R302.2, U301.5 (SPLIT)
unnamed: R301.1, U301.8 (STBY)

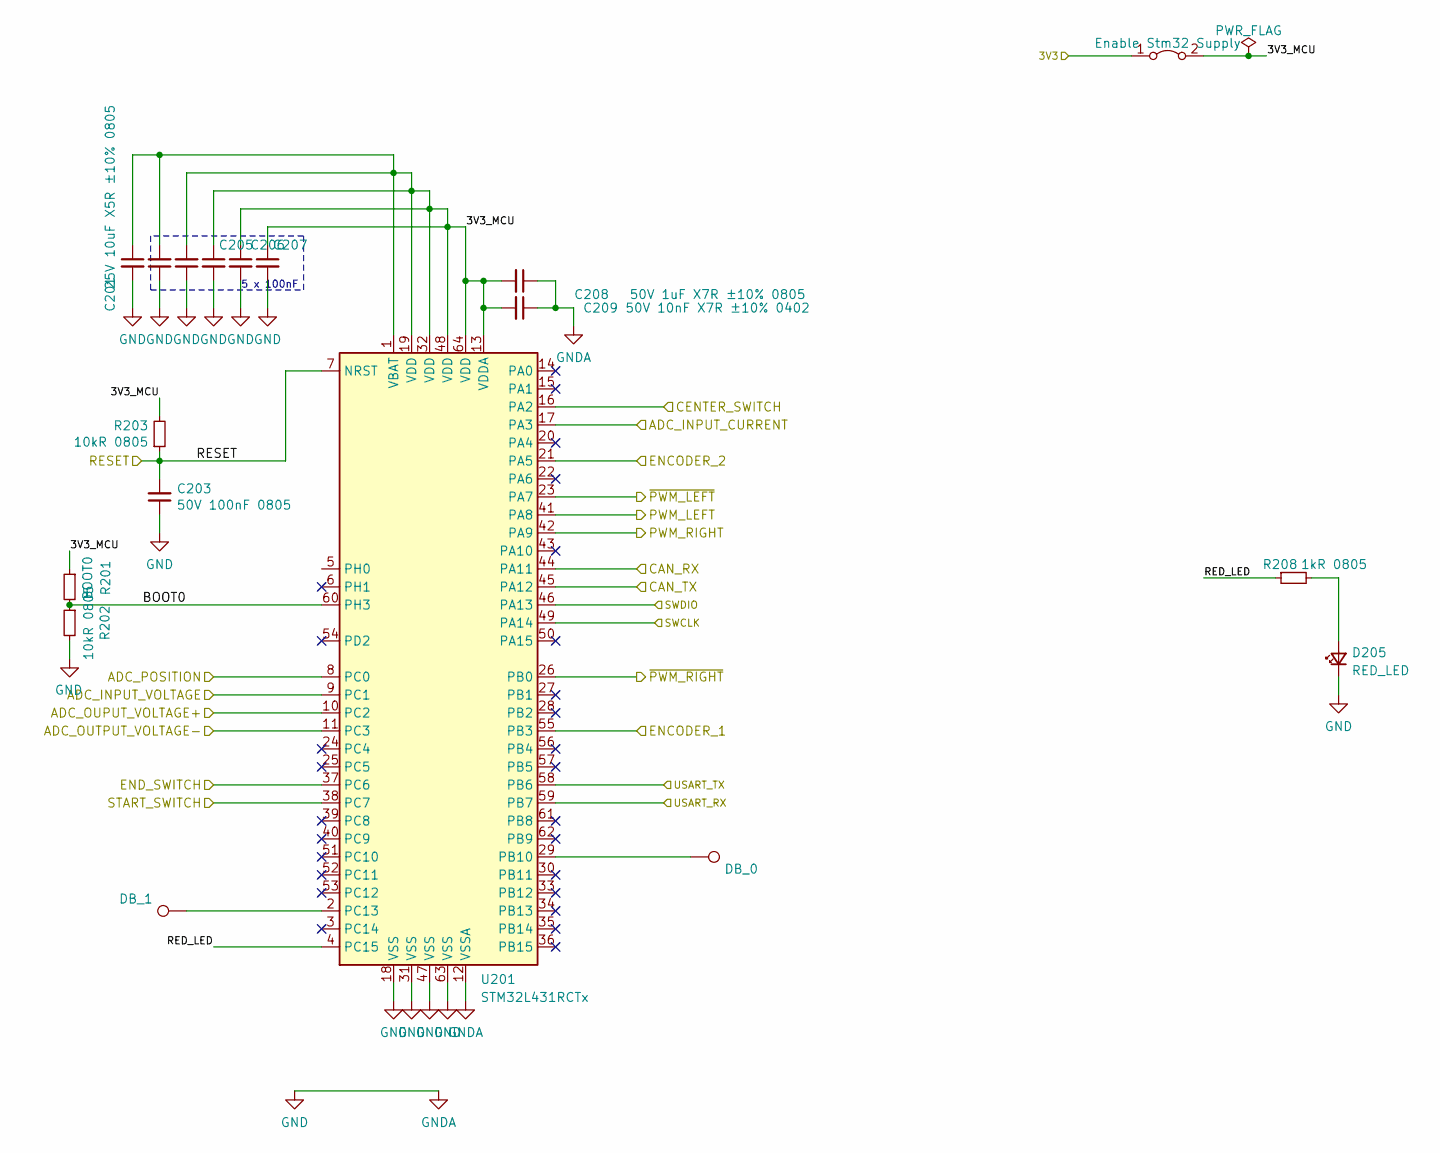
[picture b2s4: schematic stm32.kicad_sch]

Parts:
C201: 25V 10uF X5R ±10% 0805; C_0805_2012Metric_Pad1.18x1.45mm_HandSolder
C202, C203, C204: 50V 100nF 0805; C_0805_2012Metric_Pad1.18x1.45mm_HandSolder
C205, C206, C207: 50V 100nF X7R ±10% 0402; C_0805_2012Metric_Pad1.18x1.45mm_HandSolder
C208: 50V 1uF X7R ±10% 0805; C_0805_2012Metric_Pad1.18x1.45mm_HandSolder
C209: 50V 10nF X7R ±10% 0402; C_0805_2012Metric_Pad1.18x1.45mm_HandSolder
D205: RED_LED; LED_0805_2012Metric_Pad1.15x1.40mm_HandSolder
JP205: Enable Stm32 Supply; SolderJumper-2_P1.3mm_Open_TrianglePad1.0x1.5mm
R201: BOOT0; R_0805_2012Metric_Pad1.20x1.40mm_HandSolder
R202, R203: 10kR 0805; R_0805_2012Metric_Pad1.20x1.40mm_HandSolder
R208: 1kR 0805; R_0805_2012Metric_Pad1.20x1.40mm_HandSolder
TP202: DB_1; TestPoint_Pad_1.0x1.0mm
TP203: DB_0; TestPoint_Pad_1.0x1.0mm
U201: STM32L431RCTx; LQFP-64_10x10mm_P0.5mm

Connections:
+3V3: JP205.1 (A); also elsewhere on the board
/ADC_INPUT_CURRENT: U201.17 (PA3); also elsewhere on the board
/ADC_INPUT_VOLTAGE: U201.9 (PC1); also elsewhere on the board
/ADC_OUPUT_VOLTAGE+: U201.10 (PC2); also elsewhere on the board
/ADC_OUTPUT_VOLTAGE-: U201.11 (PC3); also elsewhere on the board
/ADC_POSITION: U201.8 (PC0); also elsewhere on the board
/PWM_LEFT: U201.41 (PA8); also elsewhere on the board
/PWM_RIGHT: U201.42 (PA9); also elsewhere on the board
/RESET: C203.2, R203.1, U201.7 (NRST); also elsewhere on the board
/SWCLK: U201.49 (PA14); also elsewhere on the board
/SWDIO: U201.46 (PA13); also elsewhere on the board
/USART_RX: U201.59 (PB7); also elsewhere on the board
/USART_TX: U201.58 (PB6); also elsewhere on the board
/stm32/3V3_MCU: C201.1, C202.2, C204.2, C205.1, C206.1, C207.1, C208.2, C209.2, JP205.2 (B), R201.1, R203.2, U201.1 (VBAT), U201.13 (VDDA), U201.19 (VDD), U201.32 (VDD), U201.48 (VDD), U201.64 (VDD)
/stm32/BOOT0: R201.2, R202.1, U201.60 (PH3)
/stm32/CAN_RX: U201.44 (PA11); also elsewhere on the board
/stm32/CAN_TX: U201.45 (PA12); also elsewhere on the board
/stm32/CENTER_SWITCH: U201.16 (PA2); also elsewhere on the board
/stm32/ENCODER_1: U201.55 (PB3); also elsewhere on the board
/stm32/ENCODER_2: U201.21 (PA5); also elsewhere on the board
/stm32/END_SWITCH: U201.37 (PC6); also elsewhere on the board
/stm32/RED_LED: R208.1, U201.4 (PC15)
/stm32/START_SWITCH: U201.38 (PC7); also elsewhere on the board
/~PWM_LEFT: U201.23 (PA7); also elsewhere on the board
/~PWM_RIGHT: U201.26 (PB0); also elsewhere on the board
GND: C201.2, C202.1, C203.1, C204.1, C205.2, C206.2, C207.2, C208.1, C209.1, D205.1 (K), R202.2, U201.12 (VSSA), U201.18 (VSS), U201.31 (VSS), U201.47 (VSS), U201.63 (VSS); also elsewhere on the board
unnamed: D205.2 (A), R208.2
unnamed: TP203.1, U201.29 (PB10)
unnamed: TP202.1, U201.2 (PC13)

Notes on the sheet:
5 x 100nF

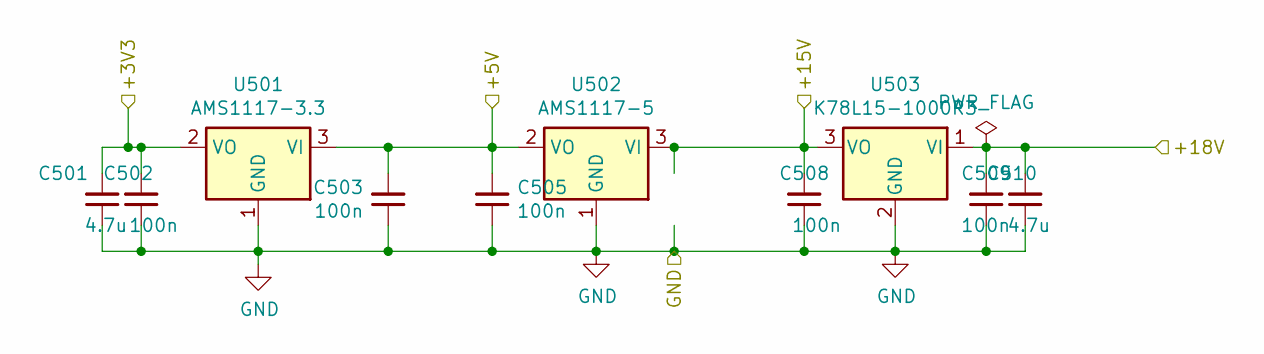
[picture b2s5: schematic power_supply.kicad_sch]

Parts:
C501, C510: 4.7u; C_1206_3216Metric_Pad1.33x1.80mm_HandSolder
C502, C503, C505, C508, C509: 100n; C_0805_2012Metric_Pad1.18x1.45mm_HandSolder
U501: AMS1117-3.3; SOT-223-3_TabPin2
U502: AMS1117-5; SOT-223-3_TabPin2
U503: K78L15-1000R3; TO-220-3_Horizontal_TabDown_SMD

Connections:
+3V3: C501.2, C502.2, U501.2 (VO); also elsewhere on the board
+5V: C503.2, C505.2, U501.3 (VI), U502.2 (VO); also elsewhere on the board
+15V: C508.2, U502.3 (VI), U503.3 (VO); also elsewhere on the board
/power_supply/+18V: C509.2, C510.2, U503.1 (VI); also elsewhere on the board
GND: C501.1, C502.1, C503.1, C505.1, C508.1, C509.1, C510.1, U501.1 (GND), U502.1 (GND), U503.2 (GND); also elsewhere on the board
